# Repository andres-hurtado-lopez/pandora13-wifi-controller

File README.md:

# pandora13-wifi-controller
A WIFI controller for the Pandora13 Box

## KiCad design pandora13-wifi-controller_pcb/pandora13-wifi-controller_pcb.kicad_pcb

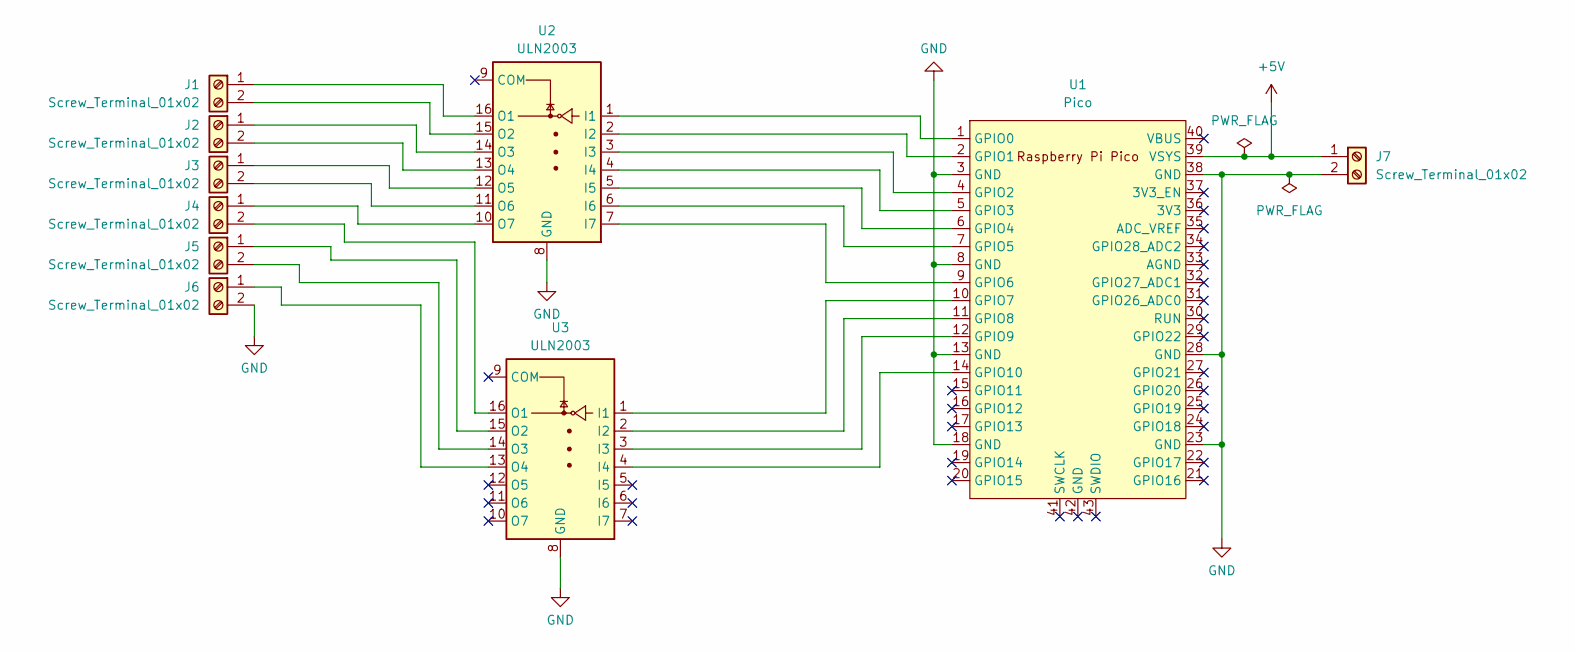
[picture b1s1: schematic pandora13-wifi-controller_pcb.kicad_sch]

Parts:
J1, J2, J3, J4, J5, J6, J7: Screw_Terminal_01x02; TerminalBlock_Altech_AK300-2_P5.00mm
U1: Pico; RPi_Pico_SMD_TH
U2, U3: ULN2003; DIP-16_W7.62mm

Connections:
+5V: J7.1, U1.39 (VSYS)
GND: J6.2, J7.2, U1.3 (GND), U1.8 (GND), U1.13 (GND), U1.18 (GND), U1.23 (GND), U1.28 (GND), U1.38 (GND), U2.8 (GND), U3.8 (GND)
unnamed: J1.1, U2.16 (O1)
unnamed: J1.2, U2.15 (O2)
unnamed: J2.1, U2.14 (O3)
unnamed: J2.2, U2.13 (O4)
unnamed: J3.1, U2.12 (O5)
unnamed: J3.2, U2.11 (O6)
unnamed: J4.1, U2.10 (O7)
unnamed: J4.2, U3.16 (O1)
unnamed: J5.1, U3.15 (O2)
unnamed: J5.2, U3.14 (O3)
unnamed: J6.1, U3.13 (O4)
unnamed: U1.1 (GPIO0), U2.1 (I1)
unnamed: U1.2 (GPIO1), U2.2 (I2)
unnamed: U1.4 (GPIO2), U2.3 (I3)
unnamed: U1.5 (GPIO3), U2.4 (I4)
unnamed: U1.6 (GPIO4), U2.5 (I5)
unnamed: U1.7 (GPIO5), U2.6 (I6)
unnamed: U1.9 (GPIO6), U2.7 (I7)
unnamed: U1.10 (GPIO7), U3.1 (I1)
unnamed: U1.11 (GPIO8), U3.2 (I2)
unnamed: U1.12 (GPIO9), U3.3 (I3)
unnamed: U1.14 (GPIO10), U3.4 (I4)

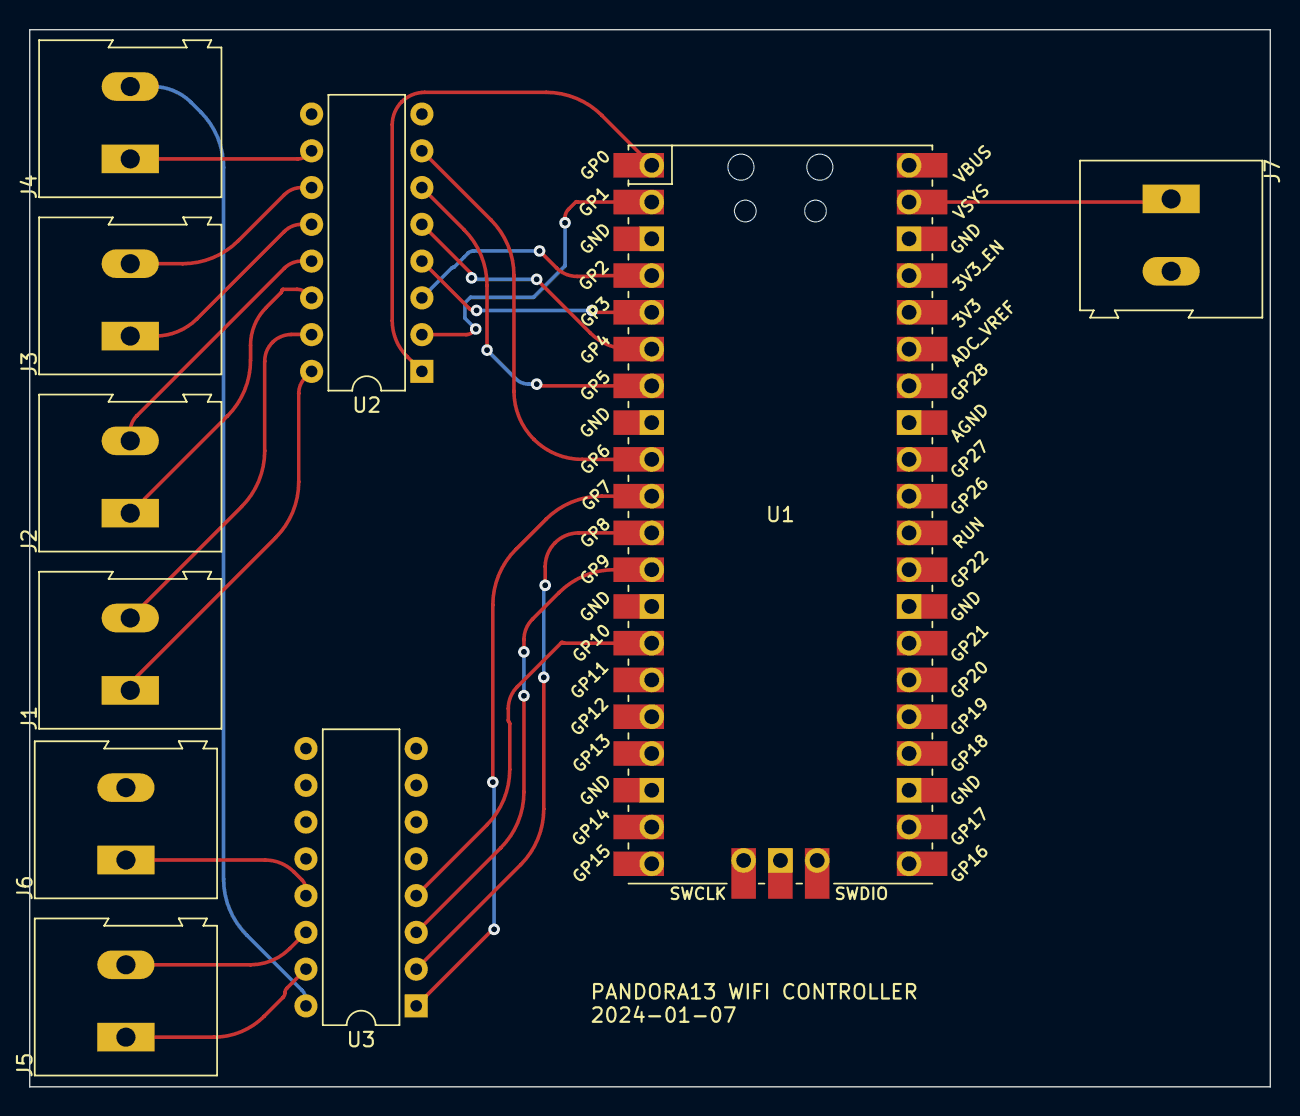
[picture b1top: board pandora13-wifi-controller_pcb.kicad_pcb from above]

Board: 2 copper layers, 85.7 x 73.0 mm, 10 parts (0 on the bottom side), 24 nets.

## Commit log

2023-12-29 First approach on building an access point with a TCP server for controlling
2023-12-29 First attempt of socket parser
2023-12-29 Some log messages modified and socket timeout increased to 5 minutes
2023-12-29 Perfboard design, datasheets, relayout of GPIO on program
2023-12-31 Task arena size increased to support all tasks in stable mode and debugs added to understand why the connections stalls after receiving the first set of bytes
2024-01-07 Unit converted into a WIFI station. PCB circuit design completed
2024-01-08 Final design sent to JLCPCB on 2024-01-07
2024-01-22 DRU for JLCPCB and routing config added
2024-01-22 -Embassy libraries updated -Pinout updated to last PCB design
2024-01-22 USer and password form bedroom added as a comment
2024-01-22 Test script added
2024-02-12 Labels on back silkscreen for each of the buttons
